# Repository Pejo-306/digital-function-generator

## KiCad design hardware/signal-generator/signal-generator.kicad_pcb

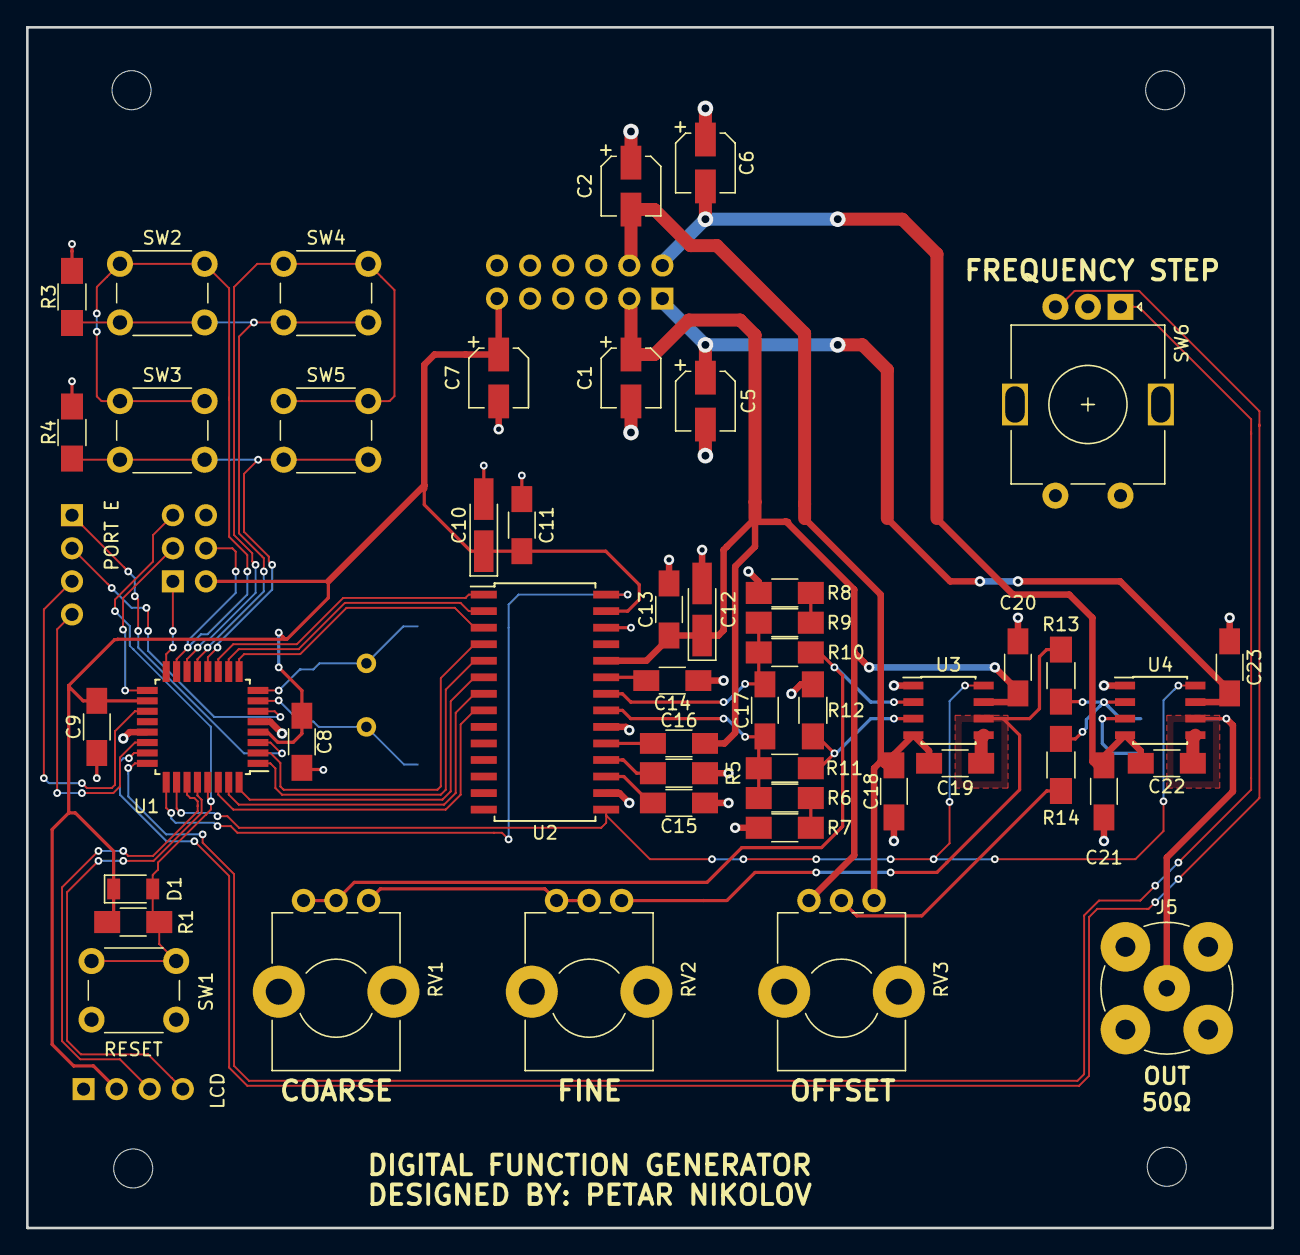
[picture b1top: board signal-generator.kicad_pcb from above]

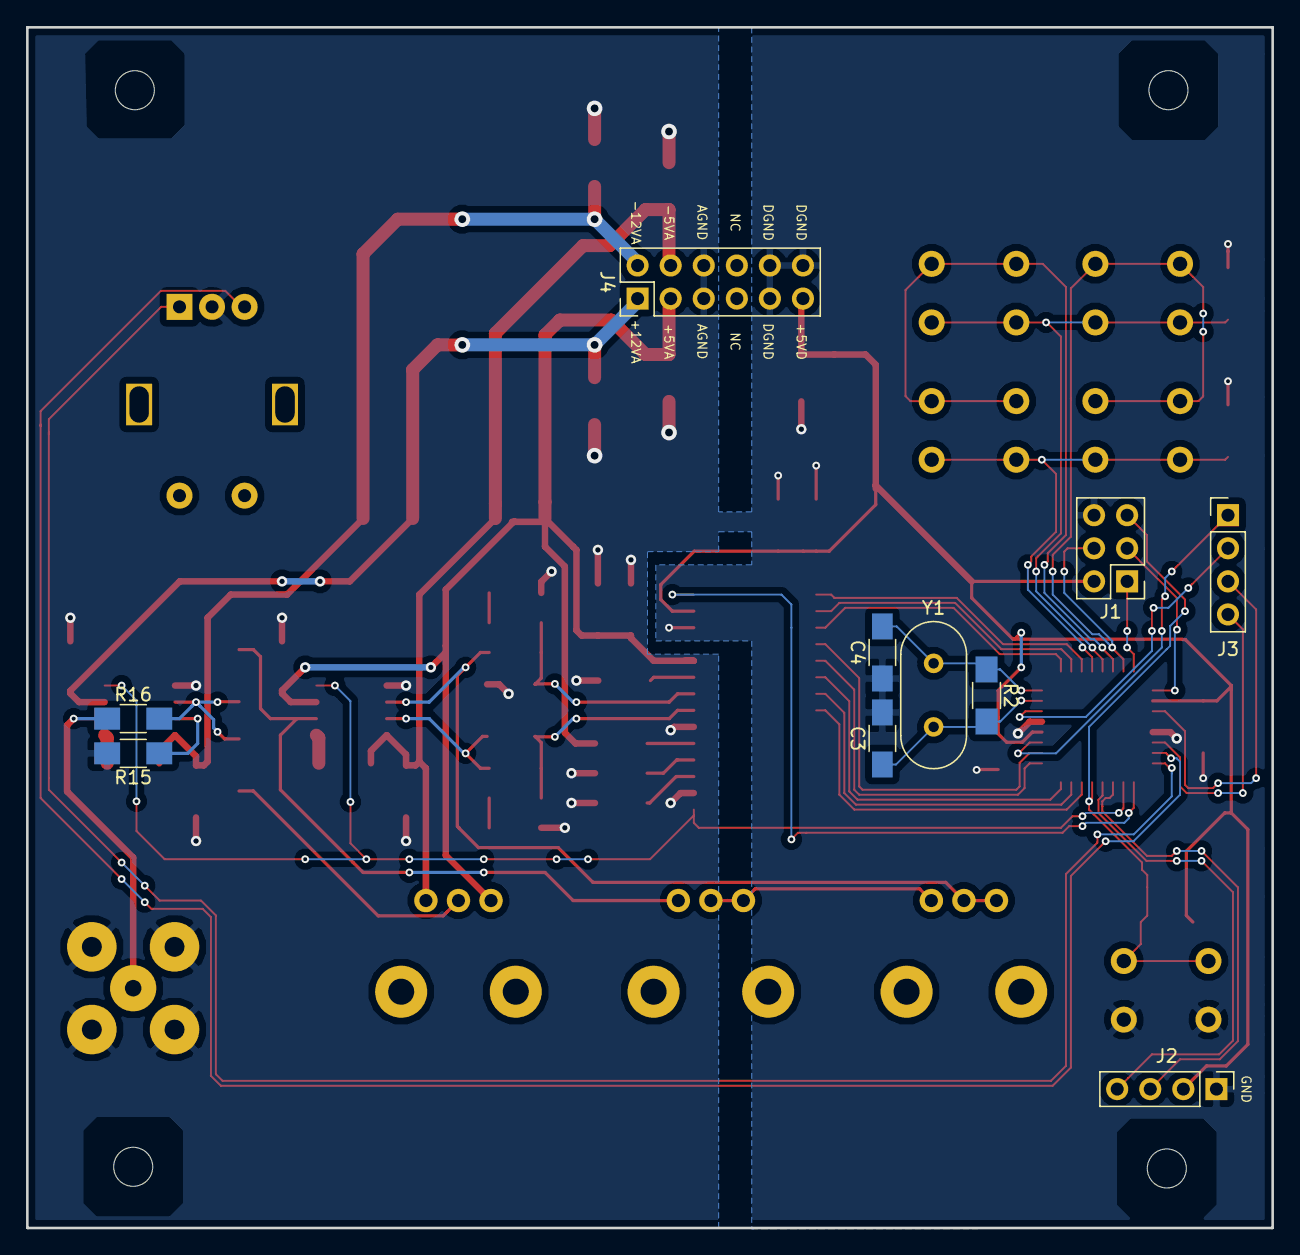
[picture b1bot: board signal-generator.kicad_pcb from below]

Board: 2 copper layers, 95.6 x 92.2 mm, 59 parts (10 on the bottom side), 51 nets.

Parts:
C1, C2, C5, C6, C7: 10uF/16V; CP_Elec_4x5.3
C3, C4: 22pF; C_1206_HandSoldering
C8, C9, C11, C13, C14, C15, C16, C18, C20, C21, C23: 100nF; C_1206_HandSoldering
C10, C12: 10uF/16V; CP_Tantalum_Case-A_EIA-3216-18_Hand
C17: 2.2nF; C_1206_HandSoldering
C19, C22: 6.8pF; C_1206_HandSoldering
D1: CD1206-S01575; D_1206
J1: AVR-ISP-6; Pin_Header_Straight_2x03_Pitch2.54mm
J2: LCD_Connector; Pin_Header_Straight_1x04_Pitch2.54mm
J3: PORT_E; Pin_Header_Straight_1x04_Pitch2.54mm
J4: Power_Supply_Rails; Pin_Header_Straight_2x06_Pitch2.54mm
J5: Output_Connector; bnc-ci
R1, R3, R4: 10k; R_1206_HandSoldering
R2: 1M; R_1206_HandSoldering
R5: 2k; R_1206_HandSoldering
R6, R8: 15R; R_1206_HandSoldering
R7, R9: 10R; R_1206_HandSoldering
R10, R11: 1k1; R_1206_HandSoldering
R12: 11k; R_1206_HandSoldering
R13, R14, R16: 3k; R_1206_HandSoldering
R15: 1k5; R_1206_HandSoldering
RV1, RV3: 10k; Potentiometer_Bourns_PTV09A-1_Horizontal
RV2: 1k; Potentiometer_Bourns_PTV09A-1_Horizontal
SW1: RESET_BUTTON; SW_PUSH_6mm_h4.3mm
SW2: START/STOP; SW_PUSH_6mm
SW3: MODE_SELECT; SW_PUSH_6mm
SW4: UP_ARROW; SW_PUSH_6mm
SW5: DOWN_ARROW; SW_PUSH_6mm
SW6: Frequency_Step_Rotary_Encoder; RotaryEncoder_Alps_EC11E-Switch_Vertical_H20mm
U1: ATmega328PB-AU; TQFP-32_7x7mm_Pitch0.8mm
U2: AD9708AR; SOIC-28W_7.5x17.9mm_Pitch1.27mm
U3, U4: AD8021ARZ; SOIC-8_3.9x4.9mm_Pitch1.27mm
Y1: 16MHz; Crystal_HC49-U_Vertical

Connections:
+5VA: C1.1, C12.1, C13.2, C16.1, C20.1, J4.3, RV3.1, U2.24, U3.7
+5VD: C7.1, C8.1, C9.1, C10.1, C11.1, D1.1, J1.2, J2.2, J4.11, R1.1, U1.4, U1.18, U2.27
+12VA: C5.1, C23.1, J4.1, U4.7
-5VA: C2.2, C18.2, C19.1, J4.4, RV3.3, U3.4
-12VA: C6.2, C21.2, C22.1, J4.2, U4.4
/BTN_COL0: J1.4, SW2.1, SW3.1, U1.15
/BTN_COL1: SW4.1, SW5.1, U1.14
/BTN_ROW0: R3.2, SW2.2, SW4.2, U1.13
/BTN_ROW1: R4.2, SW3.2, SW5.2, U1.12
/DAC/CLK: U1.25, U2.28
/DAC/DB0: U1.30, U2.8
/DAC/DB1: U1.31, U2.7
/DAC/DB2: U1.32, U2.6
/DAC/DB3: U1.1, U2.5
/DAC/DB4: U1.2, U2.4
/DAC/DB5: U1.9, U2.3
/DAC/DB6: U1.10, U2.2
/DAC/DB7: U1.11, U2.1
/DAC/SLEEP: U1.26, U2.15, U3.8, U4.8
/FREQ_STEP_A: SW6.A, U1.24
/FREQ_STEP_B: SW6.B, U1.23
/MISO: J1.1, U1.16
/Output_Circuitry/IINA: C17.1, R8.1, R10.2, U2.22
/Output_Circuitry/IINB: C17.2, R6.1, R11.1, U2.21
/Output_Circuitry/VOUT: J5.1, R16.1, U4.6
/SCL: J2.4, U1.28
/SCLK: J1.3, U1.17
/SDA: J2.3, U1.27
/XTAL1: C3.1, R2.2, U1.7, Y1.1
/XTAL2: C4.1, R2.1, U1.8, Y1.2
/~RESET: D1.2, J1.5, R1.2, SW1.2, U1.29
AGND: C1.2, C2.1, C3.2, C4.2, C5.2, C6.1, C7.2, C8.2, C9.2, C10.2, C11.2, C12.2, C13.1, C14.1, C15.1, C18.1, C20.2, C21.1, C23.2, J1.6, J2.1, J4.5, J4.6, J4.9, J4.10, J4.12, J5.2, R3.1, R4.1, R5.1, R7.2, R9.2, R12.2, R15.2, SW1.1, SW6.C, U1.5, U1.21, U2.16, U2.20, U2.26, U3.1, U4.1
unnamed: C14.2, U2.23
unnamed: C15.2, U2.17
unnamed: C16.2, U2.19
unnamed: C19.2, U3.5
unnamed: C22.2, U4.5
unnamed: J3.1, U1.3
unnamed: J3.2, U1.6
unnamed: J3.3, U1.19
unnamed: J3.4, U1.22
unnamed: R5.2, U2.18
unnamed: R6.2, R7.1
unnamed: R8.2, R9.1
unnamed: R10.1, RV1.1, RV1.2, U3.2
unnamed: R11.2, R12.1, U3.3
unnamed: R13.1, R14.1, R16.2, U4.2
unnamed: R13.2, RV2.3, U3.6
unnamed: R14.2, RV3.2
unnamed: R15.1, U4.3
unnamed: RV1.3, RV2.1, RV2.2

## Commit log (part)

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2018-11-17 [Power Supply] Create KiCad project for the power supply
2018-11-17 [Power Supply] Add +12V/-12V supply rails
    The presented dual power supply is linear in design and utilizes two
    low power complementary voltage regulators.
    The circuit is provided with reverse polarity protection on both
    the regulators' inputs via the MOSFETs Q1 and Q2. The diodes D2 and D3
    prevent any reverse current coming into the regulators' outputs from
    damaging the voltage regulators.
2018-11-18 [Power Supply] Add +5V supply rail
    The +5V supply rail is achieved via another voltage regulator. The
    latter is connected in parallel to the +12V voltage regulator.
2018-11-18 [Power Supply] Add output connector for supply rails
2018-12-09 [Power Supply] Change 1N4001 diodes to M7 diodes
    An SMD solution is preferred which is why the M7 diode was chosen. The
    latter is an SMD equivalent of 1N4007.
2018-12-09 [Signal Generator] Create KiCad project for the signal generator board
2018-12-09 [Signal Generator] Add schematic page information
2018-12-09 [Signal Generator] Setup ATMega328PB microcontroller
    The microcontroller is powered via the +5V supply rail. Also, an
    external oscillating crystal is included to set the microcontroller's
    clock speed to 16MHz.
2018-12-09 [Signal Generator] Add button to reset microcontroller
2018-12-10 [Signal Generator] Add AVR-ISP connector
    Also, added an LED to indicate a reset.
2018-12-17 [Signal Generator] Change the application's power supply
    In order to achieve high precision in high speed data conversion
    applications, the analog circuitry should not share a common power
    supply rail and a common ground as the digital circuitry of the project.
    As such, there are separate +5V rails for the digital circuitry (+5VD)
    and for the analog circuitry (+5VA), as well as different grounds
    (respectively GNDD and GNDA).
2018-12-18 [Power Supply] Change power output connector
    The new power supply schematic is to supply the following rails:
    - AGND: analog circuitry ground
    - DGND: digital circuitry ground
    - +12V/-12V dual rails (to AGND)
    - +5V/-5V dual rails (to AGND)
    - +5V digital rail (to DGND)
2018-12-20 [Signal Generator] Add output circuitry hierarchical sheet
    Also, added a few TODO comments.
2018-12-22 [Signal Generator] Design first output amplifier stage
    Firstly, the complementary current outputs of the DAC are converted into
    small voltage signals (+- 5V). These signals are passed to an amplifier
    stage, configured in a differential output configuration, where both
    small input signals are combined into one amplified single-ended signal.
    The gain of this amplifier stage can be varied via two potentiometers -
    one for coarse adjustments, one for fine.
2018-12-22 [Signal Generator] Design second output amplifier stage
    The second output amplifier stage is a summing OpAmp which adds together
    two signals - the amplified waveform and a DC offset. The latter ranges
    from +5V to -5V.
2018-12-26 [Signal Generator] Minor changes
    Changes:
    - changed bypass caps symbols in DAC schematic to non-polarized 100nF
    caps (from 0.1uF polarized)
    - add protection diode between ATMega328PB's 'RESET' pin and +5VD
    - add BNC output connector
    - remove comments
2018-12-26 [Signal Generator] Add 16x2 LCD for project's display
2018-12-26 [Signal Generator] Add control button matrix
    The four buttons are arranged in a 2x2 matrix. Their functionalities are
    described below:
    - START/STOP - begins or ends the generation of the waveform;
    - MODE_SELECT - selects whether to change the waveform type of the
    frequency of the waveform;
    - UP_ARROW - increment the value of the frequency/select the next
2019-01-09 [Signal Generator] Change pin connections
    The following connections have been altered:
    - 'PC0-PC3' -> 'PB0-PB3': change button matrix's connections to
    ATMega328PB;
    - 'PB0-PB1' -> 'PC0-PC1': change LCD's connections to ATMega328PB.
2019-01-09 [Signal Generator] Label and reorganize. Make some connections
    All functional blocks of the main schematic have been separated into
    sections enclosed by graphical lines and labeled with headers. Only the
    LCD module is not confined by such a functional block.
    The output amplifier schematic sheet has also been labeled in a similar
    manner. The amplifier has been split into two sections: the waveform
    amplifier stage and the DC offset summing amplifier stage.
2019-01-11 [Signal Generator] Add 1M resistor in parallel to crystal
    The newly added resistor ensures resonator startup.
2019-01-11 [Signal Generator] Change pin connections of LCD
    The LCD's I2C module's communication pins have been connected to the
    ATMega328PB's SDA('PC4') and SCL('PC5') pins. Furthermore, the following
    connections have been rewired to accommodate this change:
    - the rotary encoder now uses the controller's 'PC0' and 'PC1' pins;
    - the DAC's SLEEP hierarchical pin has been connected to 'PC3', the
    'CLK' - to 'PC2'.
2019-01-20 [Signal generator] Change amplifier's pots' values
    The signal amplifier stage's potentiometers have been changed to 10k+1k,
    whilst the DC offset stage's pot has been set to 10k. This change was
    implemented because the stated pot values are easier to find on the
    market. Furthermore, the amplifier's supporting resistors have been
    adjusted.
2019-01-20 [Signal generator] Increase LM318-M's slew rate
    The increased slew rate, which should now reach a typical value of
    150V/us, is achieved via a different auxiliary circuit. Refer to the
    LM318-M's datasheet for more details.
2019-01-20 [Signal generator] Change electrolytic smoothing caps to 10uF/16V
2019-01-20 [Signal generator] Add bypass capacitors to DAC
    Both tantalum and ceramic chip capacitors have been used to bypass both
    power supplies of the AD9708.
2019-01-23 [Signal generator] Include example layout of components on PCB
    The presented layout is NOT final and will definitely be altered in the
    upcoming updates. However, the final layout should roughly resemble the
    current example one.
2019-01-23 [Signal generator] Add 4 pin connector to ATMega328PB's port E
    The additional connector is optional. The latter outsources the
    microcontroller's port E which may be used for additional functionality.
2019-01-26 [Signal generator] Change power supply connector
    The power supply connector has been changed from a 8-pin one to a
    10-pin. Both additional pins connect to DGND. This allows for a better
    and more robust connector to the digital ground plane. Furthermore, it
    is necessary if external digital devices are to communicate with the
    microcontroller via the additional port E.
2019-01-26 [Signal generator] Route components no PCB
    This is not the final routing of the PCB. Further optimization is
    required. Moreover, the ground planes have not been placed.
2019-01-27 [Signal generator] Finalize PCB layout
    The presented board design is final for rev. 1. Here is a list of
    changes introduced since the last commit:
    - The power supply's connector has been changed from a 10-pin
    one to a 12-pin. The additional 2 pins are not connected(NC). The
    reasoning behind this change is that the 2 pins increase the space
    between the analog and digital supply rails, therefore allowing both
2019-02-12 Ignore all gerber and drill files. Ignore my private folder
    My private folder stores information which is not directly related to
    the project (e.g. a parts list which displays all parts' prices).
2019-02-13 [Signal Generator] Add schematic symbol for AD8021
2019-02-14 [Signal Generator] Redesign output circuitry amplifier
    I have chosen to redesign the output amplifier for a number of reasons:
    - Firstly, the main reason I choose to redesign the amplifier, I couldn't
    find some of the previously used parts at an affordable price point;
    - The previously used parts were old and somewhat unconventional by
    today's standards in my opinion;
    - The newer parts have additional functionalities such as the disable
2019-02-15 [Signal Generator] Finalize newer PCB board layout
    The new design is final for rev.2. In comparison to rev.1 the presented
    design implements the following changes:
    - The output circuitry has been redesigned from head to toe. The new
    circuitry utilizes Analog Devices's AD8021 opamp. These amplifiers have
    some advantages compared to the previous amplifiers: a more conventional
    interface, disable functionality for power efficiency, overall better
2019-04-28 [Signal Generator] Reorganize markings on F.Fab layer
    R6 and R7's value markings were swapped (i.e. R6 had '10R' next to its
    footprint, R7 had '15R' next to its footprint). The value markings have
    been swapped.
2019-04-28 [Power Supply] Start design of temporary supply. Design analog supply
    In order to program and troubleshoot the signal generator board, a
    temporary linear power supply is to be designed. It is meant to be easy
    to construct, having common THT parts.
    Currently, the analog power supply, which provides +12V/-12V and +5V/-5V
    rails (to AGND), has been designed. It is separated in its own hierarchical
    sheet.
2019-04-28 [Power Supply] Finalize design of temporary power supply
    This temporary power supply outputs the following rails:
    - +12V/-12V analog rails to AGND. These rails are connected to the
    Analog_Supply_Rails connector (J1);
    - +5V/-5V analog rails to AGND. These rails are connected to the
    Analog_Supply_Rails connector (J1);
    - +5V digital rail to DGND. This rails is outsourced to the
2019-05-06 [Power Supply] Change design of analog power supply.
    The temporary analog power supply has been redesigned so that the
    +5V/-5V rails are connected to the +12V/-12V rails in series, i.e. the
    former rails are no longer supplied directly via the transformer, but
    are now powered by the +12V/-12V rails.
    Furthermore, the digital supply's output connector's pinout has been
    changed. It now has 4 pins for +5VD and 4 pins for DGND (from 2/6).
2019-05-11 [Documentation] Start work on BG project documentation
    The project itself is to be presented as a prototype since it is not
    complete (needs proper power supply, software implementation, etc.). All
    of the missing functionality will be described in the section for future
    improvements.
    As of now, only the first page and the 'Contents' page have been
    written.
2019-05-11 [Documentation|BG] Add short description and purpose of project
2019-05-11 [Documentation|BG] Start section on technical documentation
2019-05-11 [Documentation|BG] Add power supply block diagram. Move docs to bg/ subfolder
2019-05-11 [Documentation|BG] Start section on hardware
2019-05-11 [Documentation|BG] Describe power supply's block diagram
    Changelog:
    - Change images category to 'фиг';
    - Change headings numbers from a list numbering to cross-references.
2019-05-17 [Software] Add Makefile and AVR configuration.
    Also, the project now utilizes multiple '.gitignore' files:
    - '/.gitignore': for general file ignores and non-project specific
    details;
    - '/hardware/.gitignore': ignore temporary and generated files by KiCad;
    - '/software/.gitignore': ignore compiled object files, executables,
    etc., generated when compiling C source code for AVR microcontrollers.
2019-05-25 [Documentation|BG] Add function generator block diagram
2019-06-02 [Documentation|BG] Add presentation for class
2019-06-04 [Documentation|BG] Describe power supply in details
2019-06-04 [Documentation|BG] Add power supply BOM
2019-06-22 [Documentation|BG] Document function generator's PCB and BOM.
2019-06-23 [Documentation|BG] Add prototype software block diagram.
2019-06-23 [Software] Change settling time input hold time.
    After reviewing once again AD9708's datasheet, I have concluded that the
    output settling time is not meant to be used when latching digital data
    to the DAC's input. In its place a different timing parameter is now
    utilized - the input hold time.
2019-06-23 [Documentation|BG] Restructure demo software documentation section.
    The existing documentation has been divided into two sections and a
    third one has been added which documents the ATMega328PB's fuse bytes.
2019-06-24 [Documentation|BG] Add 'Project results' and 'Future realization' sections.
